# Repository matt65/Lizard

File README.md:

# Lizard
Lizard Terrarium environment monitor

This project is to create a system to monitor the environment of our pet lizard.  The aims of this project was to:

* Monitor the temperature on the hot and cold side of the enclosure
* Turn on and off the UV light according to the sunrise and sunset
* Maintain as close to a constant temperature as possible while also having a day time and night time temperature setting

This was my first foray into the world of Python, I quite enjoyed learning the language and really enjoyed developing this project.

I have had this code running for nearly a month, it has worked nicely and I am really happy with how well it is working.

This project consists of the Python code, which itself has the main program which queries two DS18B20 waterproof temperature probes to get regular temperature reads from the hot and cold sides and uses two PowerSwith SSR Tails to turn on and off the UV light and the heat lamp.
I have also developed a PCB to interface the temperature probes and SSR tails to the Raspberry Pi, it is my plan to eventually build an enclosure (or print one), this PCB has RJ12 modular ports to make connecting and disconneting the devices much easier and less pernament.

I wasn't able to achieve it in this initial release, but I would like to add AC Zero Cross support to this project so that I could use PID ( Proportional, Integrating and Different) to maintain an ideal temperature and perhaps cause less damage to the heat lamp and use less power, currently I am cycling on and off the heat lamp, which works OK.

http://www.powerswitchtail.com/powerssr-tail
https://www.adafruit.com/product/381

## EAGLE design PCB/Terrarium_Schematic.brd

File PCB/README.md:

Lizzard Terrarium PCB
====================================
This PCB is to enable the temperature probes and SSR 
controllers to be non-pernamently connected allowing 
for ease of disasembly.
Format is EagleCAD schematic and board layout

Designed by Matthew Mulholland.  
Creative Commons Attribution, Share-Alike license, check license.txt for more information
All text above must be included in any redistribution

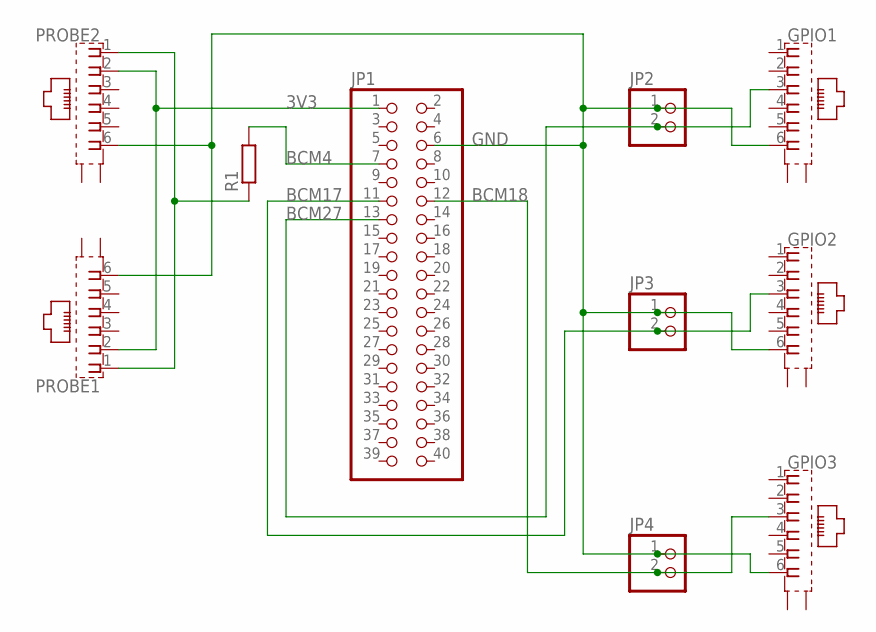
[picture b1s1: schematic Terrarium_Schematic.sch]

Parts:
GPIO1, GPIO2, GPIO3: YH-55-10
JP1: PINHD-2X20; 2X20
JP2, JP3, JP4: PINHD-1X2; 1X02
PROBE1, PROBE2: YH-55-10
R1: R-EU_0207/10; 0207/10

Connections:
3V3: JP1.1, PROBE1.2, PROBE2.2
BCM4: JP1.7, R1.2
BCM17: GPIO2.3, JP1.11, JP3.2
BCM18: GPIO3.3, JP1.12, JP4.2
BCM27: GPIO1.3, JP1.13, JP2.2
GND: GPIO1.6, GPIO2.6, GPIO3.6, JP1.6, JP2.1, JP3.1, JP4.1, PROBE1.6, PROBE2.6
unnamed: PROBE1.1, PROBE2.1, R1.1

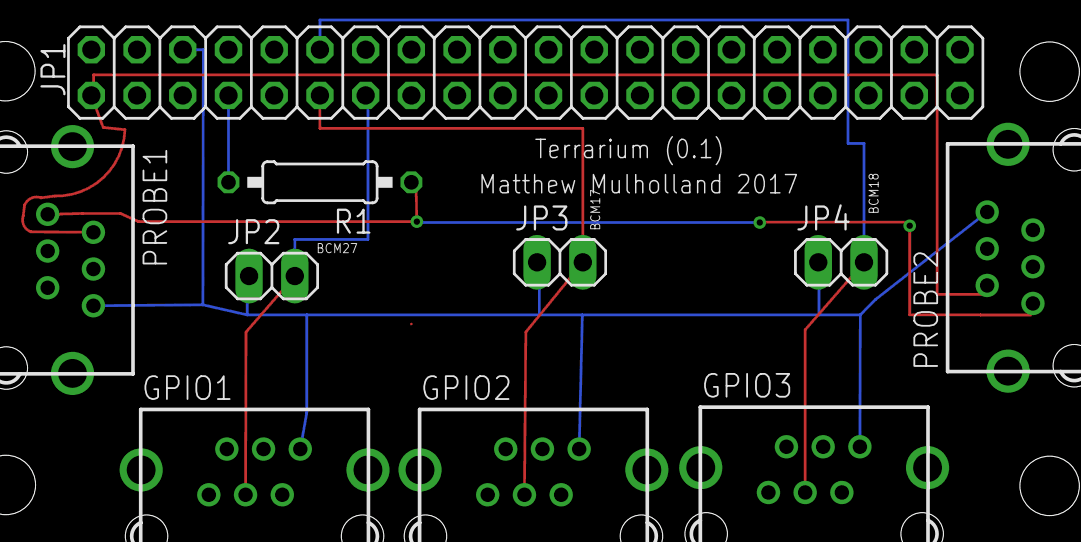
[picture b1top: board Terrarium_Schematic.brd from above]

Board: 2 copper layers, 10 parts (0 on the bottom side), 7 nets.

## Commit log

2017-08-08 PCB
    Uploaded v0.1 of the controller PCB
2017-08-08 Create LICENSE
2017-08-16 Go-Live
2017-08-17 Project Database
